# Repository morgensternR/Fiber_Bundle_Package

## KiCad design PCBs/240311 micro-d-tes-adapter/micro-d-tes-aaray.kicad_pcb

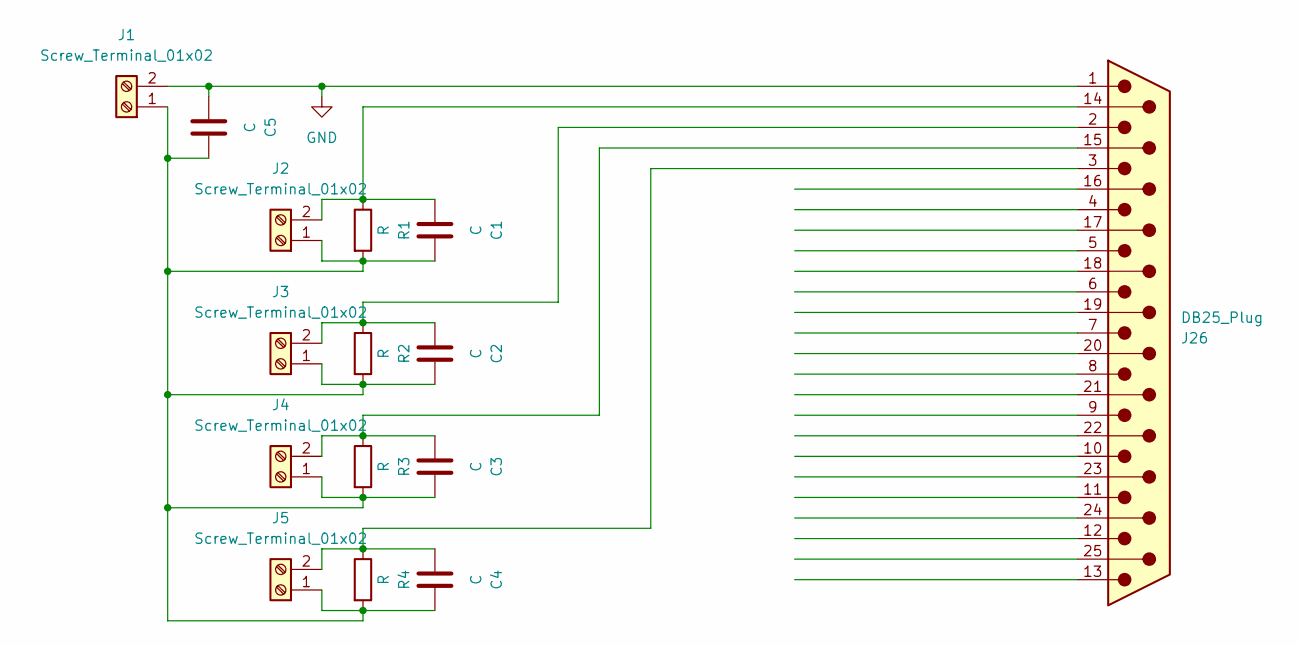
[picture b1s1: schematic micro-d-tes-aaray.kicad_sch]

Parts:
C1, C2, C3, C4, C5: C; C_0805_2012Metric; LCSC C82028
J1, J2, J3, J4, J5: Screw_Terminal_01x02; TerminalBlock_Phoenix_MKDS-1,5-2-5.08_1x02_P5.08mm_Horizont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; LCSC C8465
J26: DB25_Plug; Norcomp-380-025-113L001-microd_Updated
R1, R2, R3, R4: R; R_0805_2012Metric; LCSC C149504

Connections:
GND: C5.1, J1.2, J26.1
unnamed: C1.2, C2.2, C3.2, C4.2, C5.2, J1.1, J2.1, J3.1, J4.1, J5.1, R1.2, R2.2, R3.2, R4.2
unnamed: C1.1, J2.2, J26.14, R1.1
unnamed: C2.1, J3.2, J26.2, R2.1
unnamed: C4.1, J5.2, J26.3, R4.1
unnamed: C3.1, J4.2, J26.15, R3.1

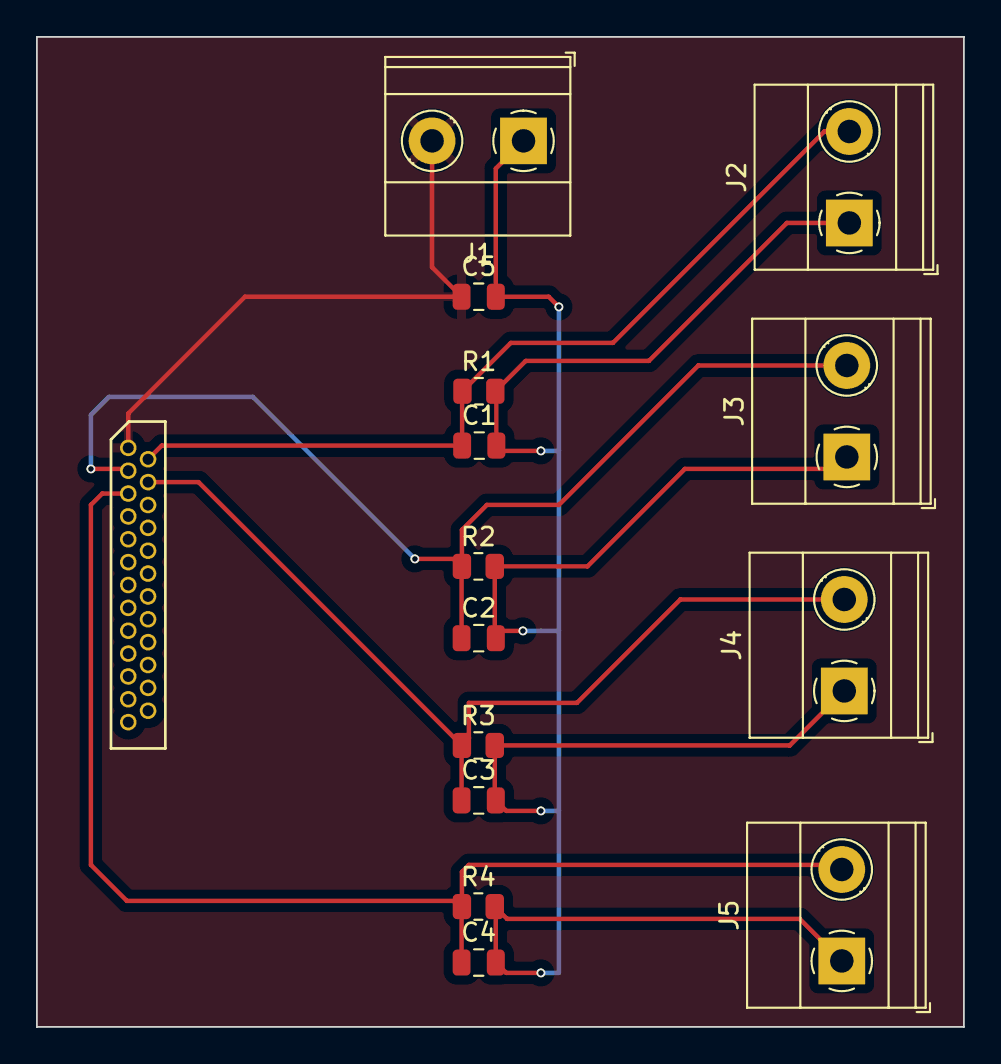
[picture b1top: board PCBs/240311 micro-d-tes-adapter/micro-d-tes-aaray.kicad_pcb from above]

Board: 2 copper layers, 51.5 x 55.0 mm, 15 parts (1 on the bottom side), 6 nets.

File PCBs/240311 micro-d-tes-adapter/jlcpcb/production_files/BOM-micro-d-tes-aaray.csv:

Comment,Designator,Footprint,LCSC
R,"R1,R2,R3,R4",R_0805_2012Metric,C149504
C,"C1,C2,C3,C4,C5",C_0805_2012Metric,C82028
Screw_Terminal_01x02,"J1,J2,J3,J4,J5","TerminalBlock_Phoenix_MKDS-1,5-2-5.08_1x02_P5.08mm_Horizontal",C8465
DB25_Plug,J26,Norcomp-380-025-113L001-microd_Updated,

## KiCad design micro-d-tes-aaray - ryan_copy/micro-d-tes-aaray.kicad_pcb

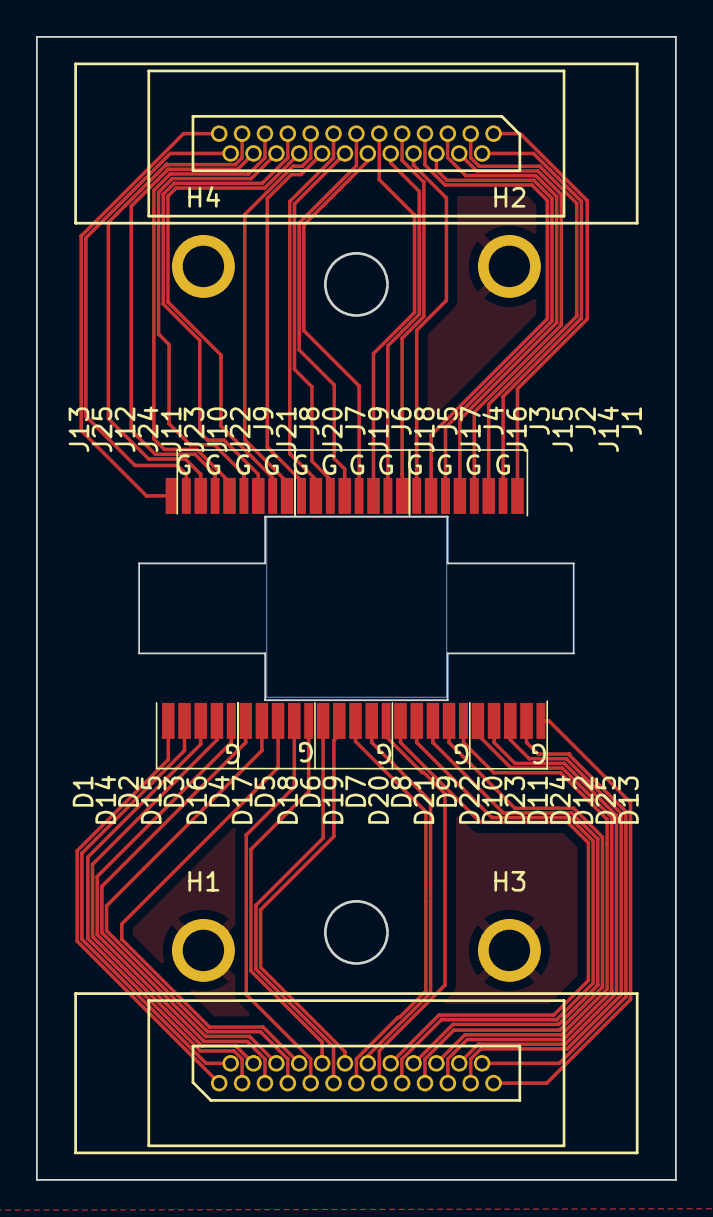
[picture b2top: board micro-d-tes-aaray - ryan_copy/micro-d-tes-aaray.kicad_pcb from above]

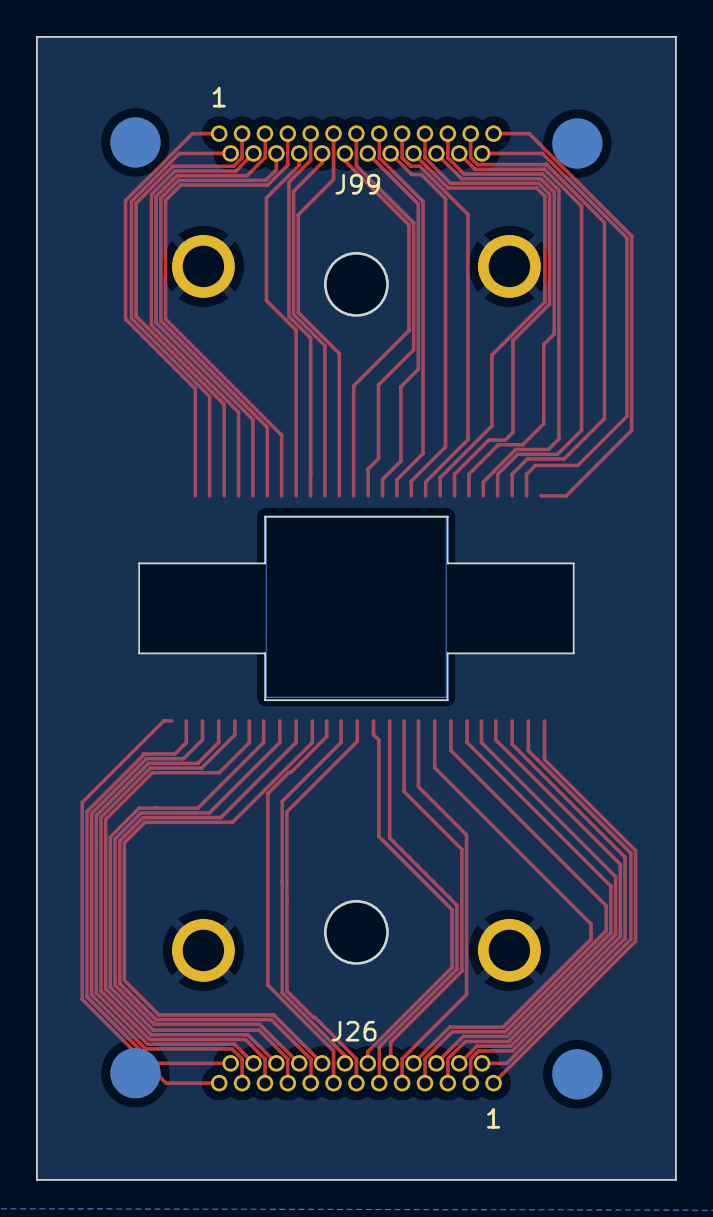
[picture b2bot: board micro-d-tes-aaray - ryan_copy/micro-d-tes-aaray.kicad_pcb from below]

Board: 4 copper layers, 35.5 x 63.5 mm, 56 parts (2 on the bottom side), 51 nets.

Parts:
D1, D2, D4, D5, D6, D7, D9, D10, D11, D12, D14, D15, D16, D17, D19, D20, D21, D22, D24, D25: Conn_01x01_Socket; SolderWirePad_1x01_SMD_0.7x2mm
D3, D8, D13, D18, D23: Conn_01x01_Socket; SolderWirePad_1x01_SMD_0.5x2mm_1
H1, H2, H3, H4: MountingHole_Pad; MountingHole_3mm_2-56_DIN965_Pad
J1, J2, J3, J4, J5, J6, J7, J8, J9, J10, J11, J12, J13: Conn_01x01_Socket; SolderWirePad_1x01_SMD_0.7x2mm
J14, J15, J16, J17, J18, J19, J20, J21, J22, J23, J24, J25: Conn_01x01_Socket; SolderWirePad_1x01_SMD_0.5x2mm_1
J26, J99: DB25_Plug; Norcomp-380-025-113L001-microd_Updated

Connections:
GND: H1.1, H2.1, H3.1, H4.1
unnamed: D1.1, J26.1
unnamed: D2.1, J26.2
unnamed: D3.1, J26.3
unnamed: D4.1, J26.4
unnamed: D5.1, J26.5
unnamed: D6.1, J26.6
unnamed: D7.1, J26.7
unnamed: D8.1, J26.8
unnamed: D9.1, J26.9
unnamed: D10.1, J26.10
unnamed: D11.1, J26.11
unnamed: D12.1, J26.12
unnamed: D13.1, J26.13
unnamed: D14.1, J26.14
unnamed: D15.1, J26.15
unnamed: D16.1, J26.16
unnamed: D17.1, J26.17
unnamed: D18.1, J26.18
unnamed: D19.1, J26.19
unnamed: D20.1, J26.20
unnamed: D21.1, J26.21
unnamed: D22.1, J26.22
unnamed: D23.1, J26.23
unnamed: D24.1, J26.24
unnamed: D25.1, J26.25
unnamed: J1.1, J99.1
unnamed: J2.1, J99.2
unnamed: J3.1, J99.3
unnamed: J4.1, J99.4
unnamed: J5.1, J99.5
unnamed: J6.1, J99.6
unnamed: J7.1, J99.7
unnamed: J8.1, J99.8
unnamed: J9.1, J99.9
unnamed: J10.1, J99.10
unnamed: J11.1, J99.11
unnamed: J12.1, J99.12
unnamed: J13.1, J99.13
unnamed: J14.1, J99.14
unnamed: J15.1, J99.15
unnamed: J16.1, J99.16
unnamed: J17.1, J99.17
unnamed: J18.1, J99.18
unnamed: J19.1, J99.19
unnamed: J20.1, J99.20
unnamed: J21.1, J99.21
unnamed: J22.1, J99.22
unnamed: J23.1, J99.23
unnamed: J24.1, J99.24
unnamed: J25.1, J99.25

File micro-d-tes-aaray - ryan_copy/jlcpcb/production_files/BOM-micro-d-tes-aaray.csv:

Comment,Designator,Footprint,LCSC
Conn_01x01_Socket,D25,SolderWirePad_1x01_SMD_0.7x2mm,
Conn_01x01_Socket,D24,SolderWirePad_1x01_SMD_0.7x2mm,
Conn_01x01_Socket,D22,SolderWirePad_1x01_SMD_0.7x2mm,
Conn_01x01_Socket,D21,SolderWirePad_1x01_SMD_0.7x2mm,
Conn_01x01_Socket,D20,SolderWirePad_1x01_SMD_0.7x2mm,
Conn_01x01_Socket,D19,SolderWirePad_1x01_SMD_0.7x2mm,
Conn_01x01_Socket,D17,SolderWirePad_1x01_SMD_0.7x2mm,
Conn_01x01_Socket,D16,SolderWirePad_1x01_SMD_0.7x2mm,
Conn_01x01_Socket,D15,SolderWirePad_1x01_SMD_0.7x2mm,
Conn_01x01_Socket,D14,SolderWirePad_1x01_SMD_0.7x2mm,
Conn_01x01_Socket,D13,SolderWirePad_1x01_SMD_0.5x2mm_1,
Conn_01x01_Socket,D8,SolderWirePad_1x01_SMD_0.5x2mm_1,
Conn_01x01_Socket,D3,SolderWirePad_1x01_SMD_0.5x2mm_1,
Conn_01x01_Socket,J25,SolderWirePad_1x01_SMD_0.5x2mm_1,
Conn_01x01_Socket,J24,SolderWirePad_1x01_SMD_0.5x2mm_1,
Conn_01x01_Socket,J23,SolderWirePad_1x01_SMD_0.5x2mm_1,
Conn_01x01_Socket,J22,SolderWirePad_1x01_SMD_0.5x2mm_1,
Conn_01x01_Socket,J21,SolderWirePad_1x01_SMD_0.5x2mm_1,
Conn_01x01_Socket,J20,SolderWirePad_1x01_SMD_0.5x2mm_1,
Conn_01x01_Socket,J19,SolderWirePad_1x01_SMD_0.5x2mm_1,
Conn_01x01_Socket,J18,SolderWirePad_1x01_SMD_0.5x2mm_1,
Conn_01x01_Socket,J17,SolderWirePad_1x01_SMD_0.5x2mm_1,
Conn_01x01_Socket,J16,SolderWirePad_1x01_SMD_0.5x2mm_1,
Conn_01x01_Socket,J15,SolderWirePad_1x01_SMD_0.5x2mm_1,
Conn_01x01_Socket,J14,SolderWirePad_1x01_SMD_0.5x2mm_1,
Conn_01x01_Socket,J13,SolderWirePad_1x01_SMD_0.7x2mm,
Conn_01x01_Socket,J12,SolderWirePad_1x01_SMD_0.7x2mm,
Conn_01x01_Socket,J11,SolderWirePad_1x01_SMD_0.7x2mm,
Conn_01x01_Socket,J10,SolderWirePad_1x01_SMD_0.7x2mm,
Conn_01x01_Socket,J9,SolderWirePad_1x01_SMD_0.7x2mm,
Conn_01x01_Socket,J8,SolderWirePad_1x01_SMD_0.7x2mm,
Conn_01x01_Socket,J7,SolderWirePad_1x01_SMD_0.7x2mm,
Conn_01x01_Socket,J6,SolderWirePad_1x01_SMD_0.7x2mm,
Conn_01x01_Socket,J5,SolderWirePad_1x01_SMD_0.7x2mm,
Conn_01x01_Socket,J4,SolderWirePad_1x01_SMD_0.7x2mm,
Conn_01x01_Socket,J3,SolderWirePad_1x01_SMD_0.7x2mm,
Conn_01x01_Socket,J2,SolderWirePad_1x01_SMD_0.7x2mm,
Conn_01x01_Socket,J1,SolderWirePad_1x01_SMD_0.7x2mm,
Conn_01x01_Socket,D23,SolderWirePad_1x01_SMD_0.5x2mm_1,
Conn_01x01_Socket,D18,SolderWirePad_1x01_SMD_0.5x2mm_1,
Conn_01x01_Socket,D12,SolderWirePad_1x01_SMD_0.7x2mm,
Conn_01x01_Socket,D11,SolderWirePad_1x01_SMD_0.7x2mm,
Conn_01x01_Socket,D10,SolderWirePad_1x01_SMD_0.7x2mm,
Conn_01x01_Socket,D9,SolderWirePad_1x01_SMD_0.7x2mm,
Conn_01x01_Socket,D7,SolderWirePad_1x01_SMD_0.7x2mm,
Conn_01x01_Socket,D6,SolderWirePad_1x01_SMD_0.7x2mm,
Conn_01x01_Socket,D5,SolderWirePad_1x01_SMD_0.7x2mm,
Conn_01x01_Socket,D4,SolderWirePad_1x01_SMD_0.7x2mm,
Conn_01x01_Socket,D2,SolderWirePad_1x01_SMD_0.7x2mm,
Conn_01x01_Socket,D1,SolderWirePad_1x01_SMD_0.7x2mm,
MountingHole_Pad,H1,MountingHole_3mm_2-56_DIN965_Pad,
MountingHole_Pad,H4,MountingHole_3mm_2-56_DIN965_Pad,
MountingHole_Pad,H3,MountingHole_3mm_2-56_DIN965_Pad,
MountingHole_Pad,H2,MountingHole_3mm_2-56_DIN965_Pad,
DB25_Plug,J99,Norcomp-380-025-113L001-microd_Updated,
DB25_Plug,J26,Norcomp-380-025-113L001-microd_Updated,

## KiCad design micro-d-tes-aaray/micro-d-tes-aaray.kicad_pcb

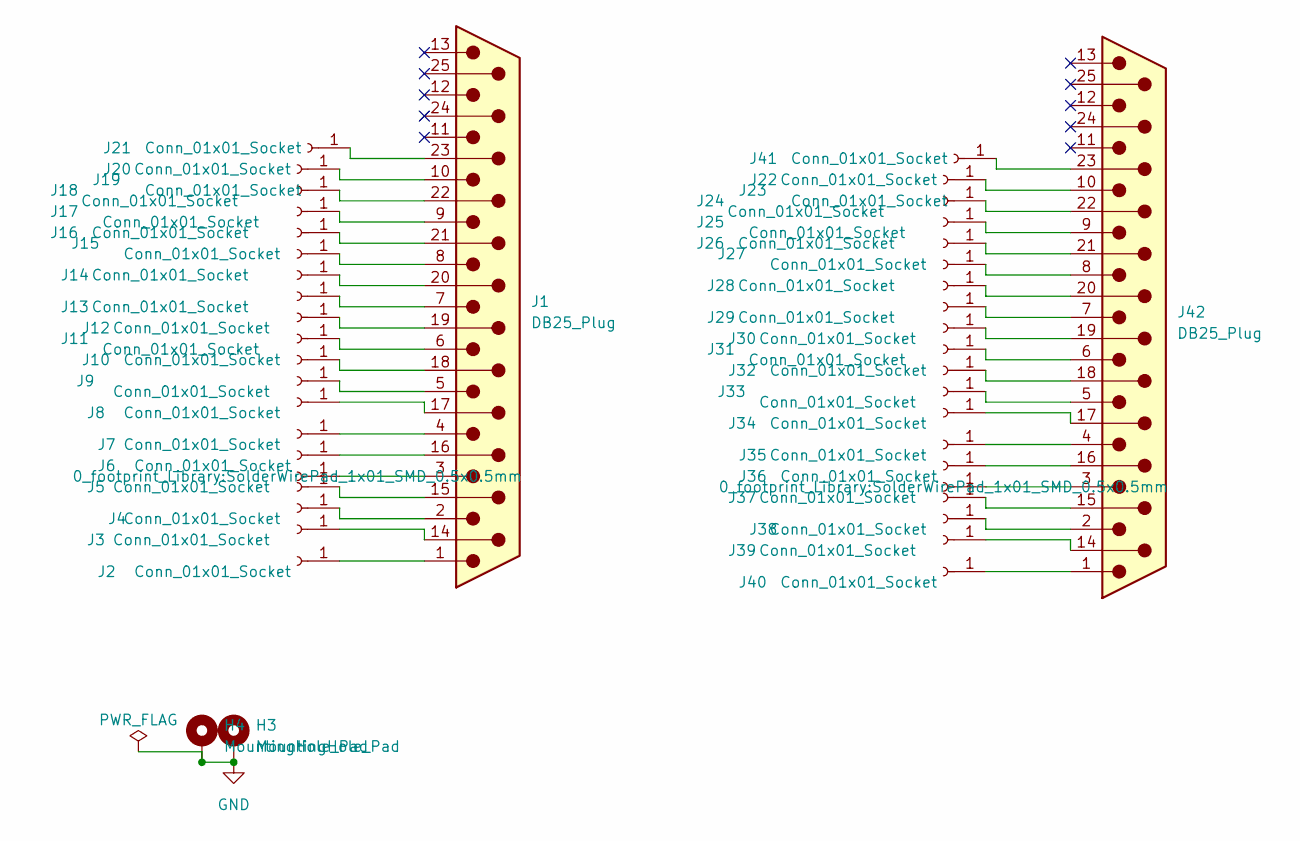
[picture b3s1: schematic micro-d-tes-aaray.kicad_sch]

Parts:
H3, H4: MountingHole_Pad; MountingHole_3mm_4-40_DIN965_Pad
J1, J42: DB25_Plug; Norcomp-380-025-113L001-microd_Updated
J2, J3, J4, J5, J6, J7, J8, J9, J10, J11, J12, J13, J14, J15, J16, J17, J18, J19, J20, J21, J22, J23, J24, J25, J26, J27, J28, J29, J30, J31, J32, J33, J34, J35, J36, J37, J38, J39, J40, J41: Conn_01x01_Socket; SolderWirePad_1x01_SMD_0.5x0.5mm

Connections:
GND: H3.1, H4.1
unnamed: J1.14, J3.1
unnamed: J1.15, J5.1
unnamed: J1.16, J7.1
unnamed: J1.17, J9.1
unnamed: J1.18, J11.1
unnamed: J1.19, J13.1
unnamed: J1.20, J15.1
unnamed: J1.21, J17.1
unnamed: J1.22, J19.1
unnamed: J1.23, J21.1
unnamed: J1.1, J2.1
unnamed: J1.2, J4.1
unnamed: J1.3, J6.1
unnamed: J1.4, J8.1
unnamed: J1.5, J10.1
unnamed: J1.6, J12.1
unnamed: J1.7, J14.1
unnamed: J1.8, J16.1
unnamed: J1.9, J18.1
unnamed: J1.10, J20.1
unnamed: J22.1, J42.10
unnamed: J23.1, J42.22
unnamed: J24.1, J42.9
unnamed: J25.1, J42.21
unnamed: J26.1, J42.8
unnamed: J27.1, J42.20
unnamed: J28.1, J42.7
unnamed: J29.1, J42.19
unnamed: J30.1, J42.6
unnamed: J31.1, J42.18
unnamed: J32.1, J42.5
unnamed: J33.1, J42.17
unnamed: J34.1, J42.4
unnamed: J35.1, J42.16
unnamed: J36.1, J42.3
unnamed: J37.1, J42.15
unnamed: J38.1, J42.2
unnamed: J39.1, J42.14
unnamed: J40.1, J42.1
unnamed: J41.1, J42.23

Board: 4 copper layers, 44 parts (0 on the bottom side), 41 nets, no tracks yet.

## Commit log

2023-04-27 repalced with old_
2023-04-27 init push
2023-04-27 update
    deleted text file
2023-04-28 CAD
    made becu clamps
    made fiber bundle
    made potential new mount design
2023-04-29 updated Cad
2023-05-13 Update
    finished old cad design
    made new cad design
    maybe finalized PCB layout
2023-05-24 added simulation
2023-05-25 update + simulations
2023-08-04 step
2023-08-04 added notes
2023-09-30 update pcb
2023-10-25 fixed 8-32s
2024-03-11 Add micro-d-tes-adapter
2025-06-20 added opticla stage to cnc if wanting to order
